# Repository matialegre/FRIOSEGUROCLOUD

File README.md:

# 🏔️ FrioSeguro - Sistema de Monitoreo de Reefers

## Ubicación
**Cerro Moro, Santa Cruz, Argentina**
- Coordenadas: 48°7'49.5768" S, 66°39'10.4231" W
- Campamento minero de oro y plata
- +400 personas alojadas

---

## 🎯 Descripción del Sistema

Sistema **COMPLETO** de monitoreo de temperatura para **Reefers** (contenedores refrigerados). Incluye firmware ESP32, apps Android (local y cloud), y dashboard web.

### Arquitectura

```
┌─────────────────────────────────────────────────────────────┐
│                    ESP32 (firmware_modular)                 │
├─────────────────────────────────────────────────────────────┤
│  📡 WiFi + mDNS                                             │
│  🌡️ Sensores DS18B20 x2 (temperatura)                       │
│  🚪 Reed Switch (puerta)                                    │
│  🔔 Relay (sirena 12V)                                      │
│  🧊 Detección automática de defrost                         │
│  🌐 Web Server + API REST                                   │
│  ☁️ Supabase (sincronización cloud)                         │
│  📨 Telegram (alertas)                                      │
└─────────────────────────────────────────────────────────────┘
         │                    │                    │
         ▼                    ▼                    ▼
    ┌─────────┐         ┌─────────┐         ┌─────────┐
    │ 📱 App  │         │ 📱 App  │         │ 🌐 Web  │
    │ Local   │         │ Cloud   │         │Dashboard│
    └─────────┘         └─────────┘         └─────────┘
         │                    │                    │
         ▼                    ▼                    ▼
    WiFi Local           Supabase              Netlify
```

### Características

✅ **Firmware modular** - Código organizado en módulos  
✅ **Funciona 100% offline** - No necesita internet  
✅ **App Android Local** - Conexión directa al ESP32 por WiFi  
✅ **App Android Cloud** - Monitoreo remoto via Supabase  
✅ **Dashboard Web** - React + Vite desplegado en Netlify  
✅ **Detección de defrost** - Ignora automáticamente descongelación  
✅ **Anti-falsos positivos** - Espera configurable antes de alertar  
✅ **Telegram** - Alertas cuando hay internet disponible  
✅ **Supabase** - Base de datos cloud en tiempo real  
✅ **Configuración editable** - Desde app o web  

---

## 📁 Estructura del Proyecto

```
campamento-parametican/
├── firmware_modular/           # Código ESP32 (USAR ESTE)
│   ├── firmware_modular.ino   # Código principal
│   ├── config.h               # Configuración hardware
│   ├── types.h                # Estructuras de datos
│   ├── storage.h              # Almacenamiento Preferences
│   ├── sensors.h              # Lectura DS18B20, DHT22
│   ├── alerts.h               # Lógica de alertas
│   ├── telegram.h             # Notificaciones Telegram
│   ├── supabase.h             # Integración Supabase
│   ├── wifi_utils.h           # Gestión WiFi
│   ├── web_api.h              # API REST
│   └── html_ui.h              # Dashboard embebido
├── android-app/               # App Android LOCAL
│   └── app/src/main/          # Conexión directa ESP32
├── android-app-cloud/         # App Android CLOUD
│   └── app/src/main/          # Conexión via Supabase
├── web-dashboard/             # Dashboard Web (React)
│   ├── src/App.jsx            # Componente principal
│   ├── src/supabaseClient.js  # Cliente Supabase
│   └── netlify.toml           # Config deploy
├── supabase/                  # Scripts SQL
│   ├── schema_v2_clean.sql    # Schema de base de datos
│   └── test_supabase.py       # Script de prueba
└── README.md
```

---

## 🔧 Hardware Necesario

### ESP32 + Sensores

| Componente | Cantidad | Pin | Precio Est. |
|------------|----------|-----|-------------|
| ESP32 DevKit | 1 | - | $8 |
| DS18B20 Waterproof | 2 | GPIO4 | $4 c/u |
| Reed Switch | 1 | GPIO5 | $1 |
| Resistencia 4.7kΩ | 1 | - | $0.10 |

### Alertas Locales

| Componente | Cantidad | Pin | Precio Est. |
|------------|----------|-----|-------------|
| Módulo Relay 5V | 1 | GPIO16 | $2 |
| Sirena 12V 110dB | 1 | Via relay | $12 |
| Fuente 12V 1A | 1 | - | $5 |
| LED Rojo | 1 | GPIO15 | $0.10 |
| LED Verde | 1 | GPIO2 | $0.10 |
| Buzzer 5V | 1 | GPIO17 | $1 |

**Total estimado: ~$40 USD**

---

## ⚡ Instalación Rápida

### 1. Configurar el ESP32

1. Abrí `firmware/config.h` y editá:
   ```cpp
   #define WIFI_SSID "TU_WIFI"
   #define WIFI_PASSWORD "TU_PASSWORD"
   #define TELEGRAM_BOT_TOKEN "TU_TOKEN"
   ```

2. En Arduino IDE:
   - Instalá las librerías: `OneWire`, `DallasTemperature`, `ArduinoJson`
   - Seleccioná: ESP32 Dev Module
   - Subí `firmware/firmware.ino`

3. Subí los archivos de `firmware/data/` a SPIFFS:
   - Herramientas → ESP32 Sketch Data Upload

### 2. Obtener la App Android

**Opción A: GitHub Actions (automático)**
1. Subí este proyecto a GitHub
2. El workflow compilará el APK automáticamente
3. Descargá desde Actions → Artifacts

**Opción B: Compilar localmente**
```bash
cd android-app
./gradlew assembleDebug
# APK en: app/build/outputs/apk/debug/
```

### 3. Configurar la App

1. Instalá el APK en los celulares
2. Abrí la app, ingresá la IP: `192.168.1.100`
3. Tocá "INICIAR MONITOREO"
4. ¡Listo! Recibirás alertas 24/7

---

## 🌐 API REST

El ESP32 expone estos endpoints:

| Endpoint | Método | Descripción |
|----------|--------|-------------|
| `/` | GET | Dashboard web |
| `/api/status` | GET | Estado actual (temp, puerta, alertas) |
| `/api/config` | GET | Configuración actual |
| `/api/config` | POST | Actualizar configuración |
| `/api/history` | GET | Historial de temperatura |
| `/api/alert/ack` | POST | Silenciar alarma |
| `/api/alert/test` | POST | Probar alerta |
| `/api/relay` | POST | Control manual del relay |

### Ejemplo de respuesta `/api/status`:

```json
{
  "sensor": {
    "temp1": -22.5,
    "temp2": -21.8,
    "temp_avg": -22.15,
    "door_open": false,
    "door_open_sec": 0,
    "sensor_count": 2,
    "valid": true
  },
  "system": {
    "alert_active": false,
    "critical": false,
    "alert_message": "",
    "relay_on": false,
    "internet": true,
    "uptime_sec": 3600,
    "total_alerts": 0,
    "wifi_rssi": -65
  },
  "location": {
    "name": "Campamento Parametican Silver",
    "lat": -48.130438,
    "lon": -66.652895
  }
}
```

---

## 📱 Telegram Bot

Bot: **@FrioSeguro_bot**

### Configurar:
1. Obtené el token del bot desde BotFather o Netlify
2. Agregá tu Chat ID en `config.h`
3. El sistema enviará alertas cuando haya internet

### Mensajes que envía:
- 🚨 **CRÍTICO**: Temperatura > -10°C
- ⚠️ **Alerta**: Temperatura > -18°C por más de 5 min
- 🚪 **Puerta**: Abierta por más de 3 min
- ✅ **Resuelto**: Cuando se normaliza

---

## 🔔 Sistema de Alertas

### Niveles de alerta:

| Nivel | Condición | Acciones |
|-------|-----------|----------|
| **Normal** | Temp ≤ -18°C | LED verde, sin alarma |
| **Warning** | Temp > -18°C | LED rojo, espera 5 min |
| **Crítico** | Temp > -10°C | Sirena + Buzzer + Telegram |
| **Puerta** | Abierta > 3 min | Alerta sin sirena |

### Anti-falsos positivos:
- Si la puerta está abierta, no alerta por temperatura
- Espera 5 minutos antes de alertar (configurable)
- La sirena es intermitente (3s on, 2s off)

---

## 🛠️ Troubleshooting

### El ESP32 no conecta al WiFi
- Verificá SSID y password en `config.h`
- Asegurate que el router esté en 2.4GHz (no 5GHz)

### No detecta sensores de temperatura
- Verificá la resistencia de 4.7kΩ entre DATA y VCC
- Probá con un solo sensor primero

### La app Android no conecta
- Verificá que el celular esté en el mismo WiFi
- Probá acceder a `http://192.168.1.100` desde el navegador

### El relay no activa la sirena
- Recordá: el relay es lógica invertida (0=ON, 1=OFF)
- Verificá la fuente de 12V para la sirena

---

## 📄 Licencia

Proyecto desarrollado para Campamento Parametican Silver.
Cerro Moro, Santa Cruz, Argentina.
"# FRIOSEGUROCLOUD" 
"# FRIOSEGUROCLOUD"

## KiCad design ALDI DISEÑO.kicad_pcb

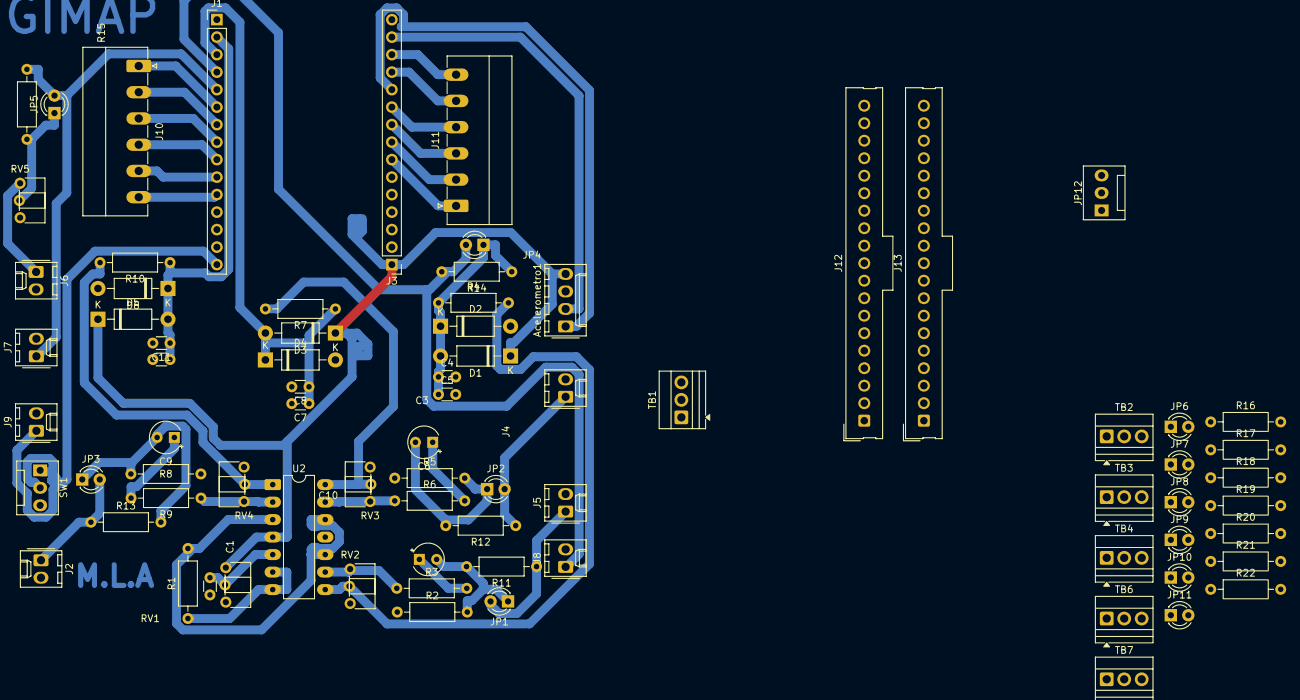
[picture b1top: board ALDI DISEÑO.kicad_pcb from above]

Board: 2 copper layers, 77 parts (0 on the bottom side), 51 nets.

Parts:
Acelerometro1: Conn_01x04; Molex_KK-254_AE-6410-04A_1x04_P2.54mm_Vertical
C1: 10nF; C_Disc_D3.0mm_W1.6mm_P2.50mm
C3, C6, C9: C_Polarized; CP_Radial_Tantal_D4.5mm_P2.50mm
C4, C7, C10: 470nF; C_Disc_D3.0mm_W1.6mm_P2.50mm
C5, C8, C11: 220nF; C_Disc_D3.0mm_W1.6mm_P2.50mm
D1, D2, D3, D4, D5, D6: 1N47xxA; D_DO-41_SOD81_P10.16mm_Horizontal
J1, J3: Conn_01x15; PinHeader_1x15_P2.54mm_Vertical
J2, J4, J5, J6, J7, J8, J9: Conn_01x02_Pin; Molex_KK-254_AE-6410-02A_1x02_P2.54mm_Vertical
J10, J11: Conn_01x06_Pin; PhoenixContact_MC_1,5_6-G-3.81_1x06_P3.81mm_Horizontal
J12, J13: Conn_01x19; Molex_SL_171971-0019_1x19_P2.54mm_Vertical
JP1, JP2, JP3, JP4, JP5, JP6, JP7, JP8, JP9, JP10, JP11: Jumper_2_Bridged; LED_D3.0mm
JP12: Jumper_3_Bridged12; FanPinHeader_1x03_P2.54mm_Vertical
R1: 10k; R_Axial_DIN0207_L6.3mm_D2.5mm_P10.16mm_Horizontal
R2, R5, R8: 3M; R_Axial_DIN0207_L6.3mm_D2.5mm_P10.16mm_Horizontal
R3, R4, R6, R7, R9, R10: 100; R_Axial_DIN0207_L6.3mm_D2.5mm_P10.16mm_Horizontal
R11, R12, R13, R14, R15: 0; R_Axial_DIN0207_L6.3mm_D2.5mm_P10.16mm_Horizontal
R16, R17, R18, R19, R20, R21, R22: 4.7k; R_Axial_DIN0207_L6.3mm_D2.5mm_P10.16mm_Horizontal
RV1, RV5: 5K; Potentiometer_ACP_CA6-H2,5_Horizontal
RV2, RV3: 10K; Potentiometer_ACP_CA6-H2,5_Horizontal
RV4: 10k; Potentiometer_ACP_CA6-H2,5_Horizontal
SW1: SW_SPST; FanPinHeader_1x03_P2.54mm_Vertical
TB1, TB2, TB3, TB4, TB6, TB7: Screw_Terminal_01x03; TerminalBlock_Xinya_XY308-2.54-3P_1x03_P2.54mm_Horizontal
U2: MCP6004; DIP-14_W7.62mm_LongPads

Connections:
3V3: R17.2, R20.2
+3.3V: Acelerometro1.4, D1.1 (K), D3.1 (K), D5.1 (K), J3.1, RV1.1, U2.4 (V+)
ADC1MICRO: C10.1, C11.1, D5.2 (A), D6.1 (K), J1.2, R10.1
ADC2MICRO: C7.1, C8.1, D3.2 (A), D4.1 (K), J1.3, R7.1
ADC3MICRO: J1.4, J8.1, JP4.2 (B), R14.2
ADC4MICRO: J1.5, J7.1, JP5.2 (B), R15.2
Bateria: J6.1, RV5.1
GND: Acelerometro1.3, C1.2, C4.2, C5.2, C7.2, C8.2, C10.2, C11.2, D2.2 (A), D4.2 (A), D6.2 (A), J1.14, J2.2, J3.2, J4.2, J5.2, J6.2, J7.2, J8.2, J9.2, R2.1, R5.1, R8.1, RV1.3, RV5.3, U2.11 (V-)
unnamed: C3.1, R3.2
unnamed: C6.1, R6.2
unnamed: C9.1, R9.2
unnamed: C4.1, C5.1, D1.2 (A), D2.1 (K), JP4.1 (A), R4.1, R14.1
unnamed: J1.6, J10.1
unnamed: J1.7, J10.2
unnamed: J1.8, J10.3
unnamed: J1.9, J10.4
unnamed: J1.10, J10.5
unnamed: J1.11, J10.6
unnamed: J9.1, SW1.1 (A)
unnamed: J3.7, J11.1
unnamed: J3.8, J11.2
unnamed: J3.9, J11.3
unnamed: J3.10, J11.4
unnamed: J3.12, J11.5
unnamed: J3.13, J11.6
unnamed: C3.2, JP1.1 (A), R2.2, R11.2
unnamed: C6.2, JP2.1 (A), R5.2, R12.2
unnamed: C9.2, JP3.1 (A), R8.2, R13.2
unnamed: JP5.1 (A), R15.1, RV5.2
unnamed: JP6.1 (A), R17.1
unnamed: JP7.1 (A), R18.1
unnamed: JP8.1 (A), R19.1
unnamed: JP9.1 (A), R20.1
unnamed: JP10.1 (A), R21.1
unnamed: JP11.1 (A), R22.1
unnamed: R4.2, RV2.2, U2.8
unnamed: R7.2, RV3.2, U2.14
unnamed: R10.2, RV4.2, U2.1
unnamed: R9.1, RV4.1, U2.2 (-)
unnamed: C1.1, RV1.2, U2.5 (+)
unnamed: R1.1, U2.6 (-), U2.7
unnamed: R3.1, RV2.1, U2.9 (-)
unnamed: R6.1, RV3.1, U2.13 (-)
OFFSET: R1.2, U2.3 (+), U2.10 (+), U2.12 (+)
SCL: Acelerometro1.2, J3.14
SDA: Acelerometro1.1, J3.11
Signal1: J2.1, JP3.2 (B), R13.1
Signal2: J4.1, JP2.2 (B), R12.1
Signal3: J5.1, JP1.2 (B), R11.1
TB6: J12.14 (Pin_12), JP11.2 (B)
VIN: J1.15, SW1.2 (B)

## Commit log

2026-01-05 Initial commit - RIFT Campamento Parametican
2026-01-05 fix: reorganizar UI, ocultar IP en modo Internet, Reefers arriba
2026-01-05 fix: lectura correcta de Supabase con devices y readings separados
2026-01-05 fix: mover declaración de manualAlert antes de checkAlerts para evitar error de compilación
2026-01-05 fix: filtrar solo dispositivos REEFER en app, excluir CARNICERIA
2026-01-11 Mejorar web dashboard: agregar IP, logos Pan American Silver y Pandemonium Tech, animaciones, aclarar estado DEFROST
2026-01-11 Add desktop viewer app with export functionality and fix IP updates in firmware
    - Complete desktop viewer app with Flask backend and Bootstrap UI
    - Export to Excel and PDF with all data fields (temp, door, defrost, relay, uptime)
    - Large visible export buttons in header
    - Filters by device, date range, and limit
    - Fixed firmware to send IP address to Supabase periodically
    - Updated device status to include IP in updates
2026-01-11 Add multi-device architecture for 7 reefers (6 production + 1 dev)
    - Add ARQUITECTURA_MULTI_DISPOSITIVO.md with complete system design
    - Update firmware config.h with new device_id format (REEFER_XX_SCZ/BHI)
    - Add config_SANTA_CRUZ.h template for production devices
    - Add update_devices_v2.sql to insert all 7 devices in Supabase
    - Device naming convention: REEFER_[NUM]_[LOCATION]
    - Production: REEFER_01_SCZ to REEFER_06_SCZ (Santa Cruz)
2026-01-11 Update web dashboard with industrial UI improvements
    - Add system state banner showing DEFROST, COOLDOWN with real timer, ALERT states
    - Add CARGANDO CONFIGURACION modal with countdown and UI blocking during config save
    - Improve reefer cards to show system state with timer
    - Add supabaseClient.js with all API functions
    - Add CSS styles for new components (state banner, config loading, reefer state)
    - Frontend only renders timer from backend, no local calculation
2026-01-11 Fix: Use fetch API directly instead of Supabase SDK to fix 401 error
2026-01-11 Fix: Keep selected device when auto-refresh updates data
2026-01-11 Fix: Keep device selection on refresh + Add DEFROST MODE and COOLDOWN TIMER display
2026-01-11 Add DEFROST MODE and COOLDOWN TIMER display to firmware, web local, apps Android and web Netlify
2026-01-11 Fix: Add cooldown_mode and cooldown_remaining_sec to /api/status endpoint
2026-01-11 Fix: Start cooldown when defrost is manually deactivated via web API
2026-01-11 Add beautiful login page with 3 hardcoded users (ANDRES, ALDI, MATI)
2026-01-11 Add netlify.toml to configure base directory for web-dashboard
2026-01-11 Add more snowflakes and improve animations for desktop view
2026-01-11 Fix login centering on desktop and add more snowflakes (60+25)
2026-01-12 Fix WiFiManager: use AP_NAME/AP_PASSWORD from config, add BOOT button reset WiFi
2026-01-12 Add Serial commands: WIFI:SSID:PASSWORD, WIFI:RESET, REBOOT, STATUS, HELP
2026-01-13 Add hardware PCB specs and 3D enclosure recommendations
2026-01-13 Update 3D enclosure links (Printables) and add EasyEDA PCB guide
2026-01-14 Add ESP reading timestamp to web dashboard with age indicator
2026-01-14 Add ESP reading timestamp to Android Cloud app with age indicator
2026-01-14 Add config sync from Supabase to ESP + browser notifications for alerts
2026-01-15 App Local: get ESP IP from Supabase first, rename apps to FrioSeguro LOCAL/CLOUD
2026-01-15 Fix alert notification logic in Local app
2026-01-15 Compiled APKs: FrioSeguro LOCAL and CLOUD
2026-01-15 feat: agregar boton Silenciar en web dashboard - Envia comando SILENCE al ESP32 via Supabase
2026-01-15 feat: agregar panel de LOGS en web dashboard - Sistema de logging centralizado - Panel flotante con filtros y auto-scroll
2026-01-15 feat: agregar cronometro de espera antes de alerta en web dashboard - Muestra tiempo restante antes de disparar alerta - Muestra estado silenciado
2026-01-16 feat: Agregar botones SILENCIAR y APAGAR RELE en todas las apps y web dashboard - Firmware: activar procesamiento comandos Supabase (RELAY_OFF, SILENCE, etc) - Firmware: reducir intervalo verificacio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
2026-01-16 feat: Iconos distintivos para cada app - LOCAL (celeste), CLOUD (verde), DEV (naranja)
2026-01-16 fix: Agregar DEVICE_ID y DEVICE_NAME faltantes en config.h
2026-01-16 fix: Evitar que config local se pise con Supabase + debounce alertas - types.h: agregar lastLocalConfigChange y lastAckTime - supabase.h: no sincronizar config si fue modificada localmente en 5min - 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
